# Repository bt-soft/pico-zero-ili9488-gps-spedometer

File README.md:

# Pico GPS Sebességmérő Motorokhoz

Ez a projekt egy fejlett Raspberry Pi Pico alapú GPS sebességmérő, amely egy ILI9488 TFT kijelzőt használ a sebesség, idő, magasság és a közeli sebességmérő kamerák (trafipaxok) megjelenítésére. A készülék kifejezetten motorkerékpár-vezetők számára lett tervezve, hogy segítse őket a biztonságos és szabályos közlekedésben.

<div style="display: flex; gap: 8px;">

</div>

## Főbb Jellemzők

### 🚀 **Sebességmérés és Navigáció**
- **Valós idejű sebességmérés** GPS adatok alapján 
- **Nagy méretű sebességmérő** vizuális megjelenítés
- **Műholdak száma** és jelerősség megjelenítése
- **Tengerszint feletti magasság** mérése és megjelenítése

### 🕐 **Időkezelés és Pozicionálás**
- **Pontos idő** megjelenítése GPS szinkronizációval
- **Automatikus időzóna** beállítás
- **Téli/nyári időszámítás** támogatása

### 🚨 **Trafipax Figyelmeztető Rendszer**
- **Intelligens sebességmérő kamera (trafipax) adatbázis** kezelése
- **Közeledési figyelmeztetés** max 1500 méteres beállítható távolságon belül (kör alapú megközelítés)
- **Vizuális riasztás**: piros háttér közeledéskor, narancssárga távolodáskor
- **Hangos figyelmeztetés** szirénával közeledés esetén
- **Távolság megjelenítése** a legközelebbi trafipaxig
- **Stabil állapotváltás** GPS pontatlansággal szembeni védelemmel

### 🎨 **Megjelenítés és Felhasználói Felület**
- **3.5" ILI9488 480x320 színes TFT kijelző**
- **Nagyméretű, jól olvasható** betűtípusok
- **Automatikusan állított háttérvilágítás** a környezeti fényerőkhöz igazodva

### 💾 **Adatkezelés és Testre Szabás**
- **LittleFS fájlrendszer** a beépített flash memóriában
- **CSV formátumú trafipax adatbázis** egyszerű frissítéshez
- **Konfigurálható figyelmeztetési távolságok**
- **Személyre szabható megjelenítési beállítások**

## Hardver Követelmények

- **Mikrokontroller:** Raspberry Pi Pico vagy Pico Zero (RP2040 alapú)
- **Kijelző:** ILI9488 3.5" 480x320 SPI TFT kijelző érintőképernyővel
- **GPS Modul:** Bármilyen UART-alapú GPS modul (pl. NEO-6M, NEO-8M), NMEA mondatok parszolása
- **Tápellátás:** 5V USB vagy külső tápegység
- **Rajz és NYÁK:** A kapcsolási rajzok, panel tervek a `kicad/` mappában

## Szoftver Architektúra

- **Fejlesztői környezet:** [PlatformIO](https://platformio.org/) a [Visual Studio Code](https://code.visualstudio.com/)-ban
- **Framework:** Arduino Framework [Raspberry Pi Pico](https://github.com/maxgerhardt/platform-raspberrypi) támogatással
- **Többmagos feldolgozás:** Dual-core RP2040 kihasználása
  - **Core 0:** Fő alkalmazás logika, kijelzőkezelés
  - **Core 1:** GPS adatfeldolgozás, háttér számítások

### Főbb Könyvtárak
- `bodmer/TFT_eSPI` - Kijelzőkezelés és sprite renderelés
- `mikalhart/TinyGPSPlus` - GPS adatfeldolgozás és koordináta számítások  
- `LittleFS` - Beépített fájlrendszer kezelés
- `NonBlockingDallas` - Hőmérséklet szenzor
- `FastLED` - Zeró intergrált RGB LED vezérlés (státusz jelzéshez, debug funkció)

## Telepítés és Üzembe Helyezés

### 1. Fejlesztői Környezet Beállítása
```bash
# Git repository klónozása
git clone https://github.com/bt-soft/pico-zero-ili9488-gps-spedometer.git
cd pico-zero-ili9488-gps-spedometer

# Visual Studio Code megnyitása
code .
```

### 2. Trafipax Adatbázis Feltöltése
A készülék kezdeti használatához fel kell tölteni a trafipax adatbázist:

```bash
# Adatbázis feltöltése LittleFS-be
pio run --target uploadfs
```

## Trafipax Adatbázis Kezelése

### Adatbázis Formátum
A `data/trafipaxes.csv` fájl formátuma:
```csv
Vármegye,Település neve,Útszám,Kilométer-szelvény/utca,GPS koordináta szélesség,GPS koordináta hosszúság
Pest,Alsónémedi,,Haraszti út 6.,47.315308,19.163705
Pest,Biatorbágy,,M1 17+000,47.468751,18.864466
Pest,Budapest,,M0,47.589436,19.142904
Pest,Budapest,,M0 14+450,47.400208,19.011840
...
```

### Adatbázis Frissítése

#### Feltöltés 
```bash
# 1. Új trafipaxes.csv elhelyezése a data/ mappában
# 2. Fájlrendszer feltöltése
pio run --target uploadfs

# 3. Készülék újraindítása (automatikus)
```

### Adatforrások
- **Magyarország:** [AutópályaMatrica.hu](https://www.autopalyamatrica.hu/fix-traffipax-lista-veda-terkep) adatai

**⚠️ Figyelmeztetés:** A trafipax adatok tájékoztató jellegűek. 

## Konfiguráció és Testreszabás
 A főbb hardveres pin hozzárendelések a `include/pins.h` fájlban találhatók, ezek igény szerint módosíthatók a saját bekötéshez.

 ### Főbb Pin Definíciók

 - **Serial1 TX/RX (GPS modul):**
   - TX: GPIO 12 (`PIN_SERIAL1_TX_NEW`)
   - RX: GPIO 13 (`PIN_SERIAL1_RX_NEW`)
   - Használat: A GPS modul csatlakoztatásához a soros portot át kell állítani ezekre a pinekre a `Serial1.setRX(PIN_SERIAL1_RX_NEW)` és `Serial1.setTX(PIN_SERIAL1_TX_NEW)` hívásokkal a `Serial1.begin()` előtt.

 - **TFT háttérvilágítás vezérlés:**
   - GPIO 1 (`PIN_TFT_BACKGROUND_LED`)
   - Automatikus fényerő szabályzás a környezeti fény alapján.

 - **Fényérzékelő:**
   - A1 (`PIN_LIGHT_SENSOR`)
   - A háttérvilágítás automatikus szabályzásához.

 - **Hőmérséklet szenzor (DS18B20):**
   - GPIO 8 (`PIN_DS18B20_TEMP_SENSOR`)

 - **Tápfeszültség mérés:**
   - VBUS: A0 (`PIN_VBUS_EXTERNAL_MEASURE_INPUT`)
   - VSYS: A2 (`PIN_VSYS_EXTERNAL_MEASURE_INPUT`)

 - **Buzzer (hangjelzés):**
   - GPIO 9 (`PIN_BUZZER`)

 A fenti pinek módosíthatók a saját hardverhez igazítva a `include/pins.h` fájlban. További testreszabási lehetőségek:
 - Trafipax figyelmeztetési távolság, hangjelzés, kijelző fényerő, stb. konfigurálható a szoftverben.

## Fejlesztői Információk

### Projekt Struktúra

```
├── src/                       # Fő forráskód és implementációk
│   ├── main.cpp               # Főprogram
│   ├── Config.cpp/.h          # Konfigurációs logika
│   ├── GpsManager.cpp/.h      # GPS kezelés
│   ├── DebugDataInspector.cpp/.h
│   ├── MessageDialog.cpp/.h
│   ├── SatelliteDb.cpp/.h
│   ├── Screen*                # Különböző képernyő logikák
│   ├── SensorUtils.cpp/.h     # Szenzor segédfüggvények
│   ├── TftBackLightAdjuster.cpp/.h
│   ├── TraffipaxManager.cpp/.h
│   ├── UIDialogBase.cpp/.h
│   ├── UIScreen.cpp/.h
│   ├── Utils.cpp/.h
│   └── ValueChangeDialog.cpp/.h
│   └── ... további modulok
├── include/                   # Header fájlok
│   ├── pins.h                 # Pin definíciók
│   ├── ... további .h fájlok
├── data/                      # LittleFS fájlok
│   └── trafipaxes.csv         # Trafipax adatbázis
├── Docs/                      # Dokumentáció
│   ├── pictures/              # Képek, renderelt ábrák
│   ├── TFT_eSPI/              # Kijelző setup és példák
│   └── trafipaxes.csv         # Minta adatbázis
├── kicad/                     # Hardver tervek
│   ├── pico-gps-spedometer/   # Fő kapcsolási rajzok, PCB
│   ├── pico-gps-spedometer-accu/ # Akkumulátoros verzió
├── platformio.ini             # PlatformIO konfiguráció
├── upload_fs.py               # Fájlrendszer feltöltő script
├── info.txt                   # Projekt információk
└── .vscode/                   # VS Code beállítások
```

**Fontos:** A TFT_eSPI könyvtár megfelelő működéséhez a `Docs/TFT_eSPI/User_Setup.h` fájlt be kell másolni a következő helyre:

```
.pio\libdeps\pico\TFT_eSPI\User_Setup.h
```

Ez biztosítja, hogy a kijelző beállítások megfelelően érvényesüljenek a build során. Ha módosítod a kijelző vagy a pinek konfigurációját, ezt a fájlt frissíteni kell és újra bemásolni a fenti könyvtárba.

---
**Fejlesztő:** BT-Soft  
**Blog:** [https://electrodiy.blog.hu/](https://electrodiy.blog.hu/)  
**GitHub:** [https://github.com/bt-soft](https://github.com/bt-soft)  

---

**⚠️ Biztonsági figyelmeztetés:** Ez az eszköz csak tájékoztató célokat szolgál. A közlekedési szabályok betartása a vezető felelőssége. A készülék használata nem mentesít a figyelmes és szabályos vezetés kötelezettsége alól.

## Képek a POC projektről

<div style="display: flex; gap: 8px;">

</div>

<div style="display: flex; gap: 8px;">

</div>

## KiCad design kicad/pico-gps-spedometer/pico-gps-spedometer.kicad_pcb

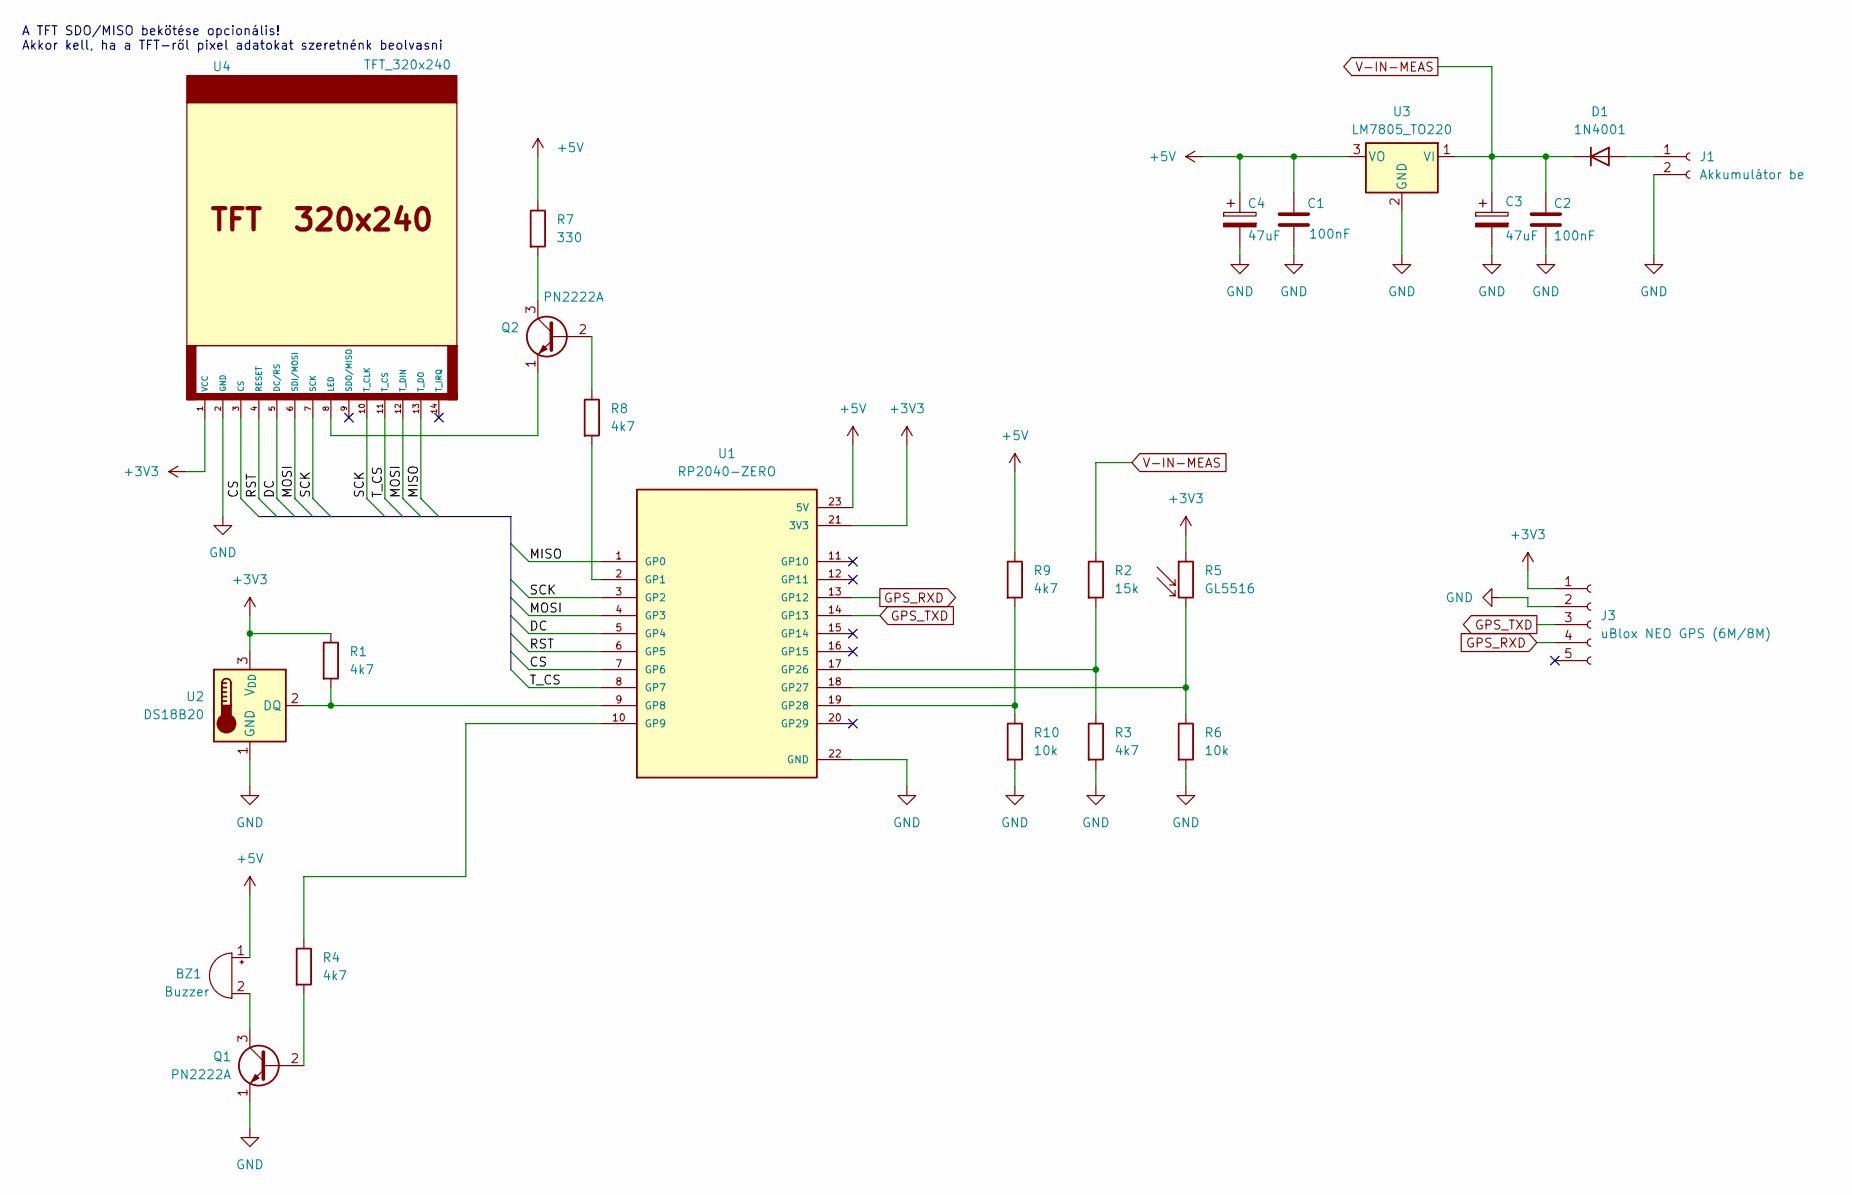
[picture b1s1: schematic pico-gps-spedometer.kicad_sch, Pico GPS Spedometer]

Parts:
BZ1: Buzzer; Buzzer_12x9.5RM7.6
C1, C2: 100nF; C_Disc_D5.0mm_W2.5mm_P2.50mm
C3, C4: 47uF; CP_Radial_D7.5mm_P2.50mm
D1: 1N4001; D_DO-41_SOD81_P10.16mm_Horizontal
J1: Akkumulátor be; PinHeader_1x02_P2.54mm_Vertical
J3: uBlox NEO GPS (6M/8M); PinSocket_1x05_P2.54mm_Vertical
Q1, Q2: PN2222A; TO-92_Inline
R1, R3, R4, R8, R9: 4k7; R_Axial_DIN0204_L3.6mm_D1.6mm_P7.62mm_Horizontal
R2: 15k; R_Axial_DIN0204_L3.6mm_D1.6mm_P7.62mm_Horizontal
R5: GL5516; PinHeader_1x02_P2.54mm_Vertical
R6, R10: 10k; R_Axial_DIN0204_L3.6mm_D1.6mm_P7.62mm_Horizontal
R7: 330; R_Axial_DIN0204_L3.6mm_D1.6mm_P7.62mm_Horizontal
U1: RP2040-ZERO; MODULE_RP2040-ZERO; PARTREV NA
U2: DS18B20; PinHeader_1x03_P2.54mm_Vertical
U3: LM7805_TO220; TO-220-3_Horizontal_TabDown
U4: TFT_320x240; PinSocket_1x14_P2.54mm_Vertical

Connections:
+3V3: J3.1, R1.1, R5.1, U1.21 (3V3), U2.3 (V_{DD}), U4.1 (VCC)
+5V: BZ1.1 (+), C1.1, C4.1, R7.1, R9.1, U1.23 (5V), U3.3 (VO)
/CS: U1.7 (GP6), U4.3 (CS)
/DC: U1.5 (GP4), U4.5 (DC/RS)
/MISO: U1.1 (GP0), U4.13 (T_DO)
/MOSI: U1.4 (GP3), U4.6 (SDI/MOSI), U4.12 (T_DIN)
/RST: U1.6 (GP5), U4.4 (RESET)
/SCK: U1.3 (GP2), U4.7 (SCK), U4.10 (T_CLK)
/T_CS: U1.8 (GP7), U4.11 (T_CS)
GND: C1.2, C2.2, C3.2, C4.2, J1.2, J3.2, Q1.1 (E), R3.2, R6.2, R10.2, U1.22 (GND), U2.1 (GND), U3.2 (GND), U4.2 (GND)
GPS_RXD: J3.4, U1.13 (GP12)
GPS_TXD: J3.3, U1.14 (GP13)
unnamed: BZ1.2 (-), Q1.3 (C)
unnamed: D1.2 (A), J1.1
unnamed: Q1.2 (B), R4.2
unnamed: Q2.2 (B), R8.1
unnamed: Q2.3 (C), R7.2
unnamed: Q2.1 (E), U4.8 (LED)
unnamed: R8.2, U1.2 (GP1)
unnamed: R1.2, U1.9 (GP8), U2.2 (DQ)
unnamed: R4.1, U1.10 (GP9)
unnamed: R2.2, R3.1, U1.17 (GP26)
unnamed: R5.2, R6.1, U1.18 (GP27)
unnamed: R9.2, R10.1, U1.19 (GP28)
V-IN-MEAS: C2.1, C3.1, D1.1 (K), R2.1, U3.1 (VI)

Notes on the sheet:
A TFT SDO/MISO bekötése opcionális! Akkor kell, ha a TFT-ről pixel adatokat szeretnénk beolvasni

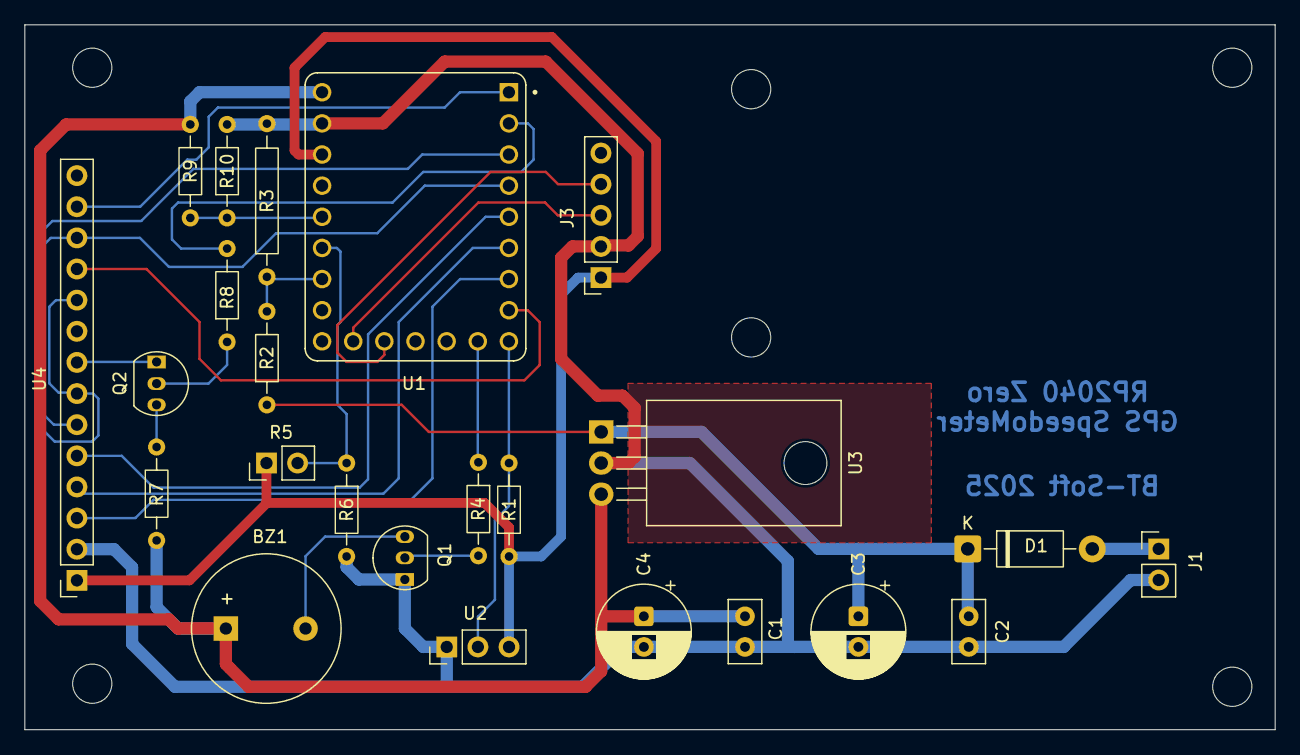
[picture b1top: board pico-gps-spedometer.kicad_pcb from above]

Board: 2 copper layers, 102.0 x 57.5 mm, 24 parts (0 on the bottom side), 25 nets.

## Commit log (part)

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2025-01-04 Működő verzió
2025-08-09 Add support for TFT display and GPS functionality with daylight saving adjustments
    - Created a stripped down User_Setup.h for ILI9488 display configuration.
    - Implemented DaylightSaving class to handle time zone and summer time corrections.
    - Added commons.h for color schemes and font sizes.
    - Developed linearMeter.h for vertical and horizontal linear meters.
    - Created ringMeter.h for displaying values in a circular format with rainbow colors.
    - Configured platformio.ini for project dependencies and build settings.
2025-08-09 Enhance documentation and comments in linearMeter and ringMeter; update speed value handling in main.cpp
2025-08-09 Enhance verticalLinearMeter and ringMeter functions for improved text rendering and color handling
2025-08-09 Remove unnecessary debug serial prints and improve temperature change handling comments
2025-08-10 Fix speed value handling in displayValues function for accurate ringMeter display
2025-08-10 Refactor verticalLinearMeter to use TFT_eSprite for improved rendering and memory management
2025-08-10 Remove random speed value generation for accurate display in displayValues function
2025-08-10 Remove lock file for pico-gps-spedometer PCB
2025-08-10 Add ASCII conversion utility and demo simulation for Trafipax alerts
2025-08-12 egyoldalas nyák
2025-08-14 Update alert bar height and adjust text positioning in Trafipax alert display
2025-08-14 Implement Trafipax demo functionality with simulation of approach and departure phases
2025-08-16 Update README to enhance project description, features, hardware requirements, software architecture, and installation instructions
2025-08-16 Remove obsolete files from the project
    - Deleted map.dat and version.dat from the Docs/tiveda directory as they are no longer needed.
    - Removed an outdated backup zip file of the pico GPS speedometer from the kicad backups directory.
2025-08-16 Add splash screen and display version information on startup
2025-08-16 Enable demo mode for speed and satellite values in displayValues function
2025-08-17 Remove commented-out modern splash screen code for cleaner implementation
2025-08-17 Add TrafipaxManager class and related functionality
    - Introduced TrafipaxManager class to handle traffic camera data management.
    - Removed TafipaxList class and its associated files.
    - Implemented methods for loading traffic camera data from CSV, checking proximity, and demo functionalities.
    - Updated ConfigData structure to include gpsTrafiAlarmEnabled flag.
    - Adjusted main application logic to utilize TrafipaxManager for traffic camera operations.
2025-08-17 Refactor Trafipax configuration and alert handling: - Update Config_t structure to reorder gpsTrafiAlarmDistance and gpsTrafiAlarmEnabled. - Change MAX_TAFIPAX to MAX_TRAFIPAX_COUNT for consistency. 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
2025-08-17 Add demo mode functionality to TrafipaxManager and main logic
2025-08-17 Enhance Settings and Button classes with new functionalities for brightness control and UI improvements
2025-08-17 Refactor Settings class for improved button layout and add screen title rendering functionality
2025-08-17 Enhance Button and Settings classes with visual feedback, layout optimizations, and modern design elements
2025-08-17 Refactor code structure and remove redundant functions for improved readability and maintainability
2025-08-17 Refactor GPS GSV message handling and streamline satellite data processing
2025-08-17 Refactor GPS GSV message handling to improve satellite data processing and tracking accuracy
2025-08-23 Refactor GPS handling and add satellite database management; rename adjust method to loop in TftBackLightAdjuster, implement GpsManager and SatelliteDb classes for improved satellite data processing 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
2025-08-23 Update LED color indication and improve satellite database handling in GpsManager
2025-08-23 Initialize FastLED for LED control in GpsManager and fix typo in LED blinking comment
2025-08-23 Add debugging options for GPS data and RGB LED control; remove unused ConfigData.h
2025-08-23 Fix icon positioning in drawContent method; adjust GPS accuracy and speedometer icon placements for improved layout.
2025-08-23 Add max speed tracking and display in handleOwnLoop; enhance speedometer feedback with dynamic updates
2025-08-23 Add sensor utility integration for battery and temperature readings in handleOwnLoop; update vertical linear meters to reflect real-time values.
2025-08-23 Refactor DebugDataInspector header file for improved clarity and maintainability
2025-08-23 Update sensor initialization and maintenance in main setup and loop; add new main.cpp_dallas file for reference
2025-08-23 Refactor SensorUtils to implement NonBlockingDallas for temperature handling; update initialization and loop methods
2025-08-23 Refactor SensorUtils to use static objects for Dallas temperature sensor; re-enable sensor maintenance in main loop
2025-08-24 Adjust text positioning for units and date/time display; improve layout consistency
2025-08-24 Add temperature mode state and sprite update timer; adjust sensor cache timeout
2025-08-24 Rename temperatureMode to externalTemperatureMode for clarity; update related logic and text positioning
2025-08-24 Add Info and Setup screens with navigation buttons; refactor layout components
2025-08-24 Implement ScreenSats class for detailed GPS satellite display; refactor screen management and update related components
2025-08-24 Refactor ScreenSats class: remove unused direct drawing methods and implement getColorBySnr function for cleaner code
2025-08-24 Enhance satellite data management: add sorting options and update UI interactions for better user experience
2025-08-24 Refactor screen setup classes: streamline back button functionality and improve layout component organization
2025-08-24 Refactor configuration and screen setup: improve GPS settings organization and update button labels for clarity
2025-08-24 Refactor ScreenTFTSetup: add manual brightness button and enhance auto brightness functionality
2025-08-24 Refactor ValueChangeDialog: enhance safe arithmetic checks and ensure button redraw on state change
2025-08-29 Refactor ScreenGPSSetup and related components: enhance layout and button functionality, add GPS traffic alarm distance adjustment
2025-08-29 Enhance GPS display: adjust satellite count position and add current GPS mode display
2025-08-29 Add DisplayData structure and data collection methods for real and demo modes
2025-08-29 Update demo mode GPS accuracy: adjust HDOP range to improve data realism
2025-08-29 Update splash screen: change font style and size for traffic count display
2025-08-29 Update date and time display formatting: adjust text padding and reposition time string for improved layout
2025-08-30 Refactor header guards to use #pragma once for consistency across multiple files
    - Updated all header files to replace traditional include guards with #pragma once for improved readability and maintainability.
    - Modified GpsManager to enhance LocalDateTime structure with separate validity flags for time and date.
    - Adjusted button dimensions in ValueChangeDialog for better UI consistency.
    - Updated button gap constant in MessageDialog to use the newly defined BUTTONS_GAP.
    - Improved comments and documentation for clarity in various functions across multiple files.
2025-08-30 Update text padding in handleOwnLoop for improved layout
2025-08-30 Refactor TraffipaxManager: Update demo handling logic and replace static demo coordinates with dynamic values
2025-08-30 Refactor TraffipaxManager: Improve debug output for demo traffic selection
2025-08-30 Remove debug wait for serial definition from defines.h
2025-08-30 Refactor TraffipaxManager: Enhance debug output formatting in demo phase processing
2025-08-30 Refactor ScreenMain and ScreenDebugSetup: Rename batteryVoltage to busVoltage for clarity and update layout logic for button positioning
2025-08-30 Refactor GpsManager: Update LED pin definitions and initialization for clarity and consistency
2025-08-30 Refactor Config: Update comment for clarity regarding internal LED behavior
2025-08-31 Refactor ScreenMain and UIScreen: Optimize state variables, extract demo logic, and implement UI value update helper function
2025-08-31 Refactor ScreenInfo: Improve formatting and readability of UIButton creation in layoutComponents
2025-08-31 Refactor ScreenSats: Reorder includes and remove redundant comment on table width
2025-08-31 Refactor Siren Handling: Update siren parameters for improved alert functionality and ensure non-blocking siren handling in the main loop
2025-08-31 Refactor ScreenSats and ScreenMain: Improve button layout and text positioning for better UI clarity
2025-08-31 Refactor ScreenMain: Adjust calendar and time string positioning for improved UI alignment
2025-08-31 Refactor ScreenInfo: Enhance drawContent method to add second column for heap memory statistics
2025-08-31 Refactor ScreenSats: Improve satellite table display and add beeper functionality on header touch events
2025-08-31 Refactor ScreenInfo: Update text color and position for GPS Speedometer display
2025-08-31 Refactor ScreenMain: Implement dark button color scheme for Info and Setup buttons
2025-09-01 Refactor: Optimize string handling with buffers across multiple screens and utilities
2025-09-04 Refactor TftBackLightAdjuster: Add debug log for backlight brightness adjustment
2025-09-05 Refactor CPU frequency settings: Update F_CPU to 133MHz and remove legacy configuration
2025-09-06 Refactor drawContent and handleOwnLoop: Improve formatting and add external voltage reading
2025-09-06 Refactor handleOwnLoop: Add conditional GPS boot time display logic
2025-09-06 Refactor screensaver logic and backlight control: Enhance screensaver activation conditions and adjust backlight management during screensaver state
2025-09-06 Remove debug logging for backlight control in loop1
2025-09-06 Refactor ScreenScreenSaver: Update variable types for position calculations and adjust font size for improved layout
2025-09-06 Refactor configuration handling: Move external temperature and voltage modes to ConfigData structure, update references in ScreenMain and ScreenScreenSaver
2025-09-10 Update visible layers and fix footprint mismatch in pico-gps-spedometer project
    - Changed the visible layers setting in the .kicad_prl file to include a new layer.
    - Updated the footprint mismatch entry in the .kicad_pro file to correct the dimensions for a specific component.
2025-09-10 readme.md
2025-09-12 Add lock file for pico-gps-spedometer schematic to prevent concurrent edits
2025-09-12 Update README.md to include detailed hardware pin assignments and configuration options for GPS and TFT display
2025-09-12 Update README.md to include instructions for TFT_eSPI library setup and configuration
2025-09-12 Fix formatting in README.md by adding a separator before developer information
2025-09-12 Update image display in README.md for better visibility
2025-09-12 Reorder images in README.md for improved layout consistency
2025-09-12 Reorganize image layout in README.md for improved display and consistency
2025-09-12 Fix duplicate image entries in README.md for improved layout consistency
2025-09-14 Remove outdated backup zip files for pico-gps-spedometer
2025-09-14 Refactor sensor initialization and maintenance to setup1 and loop1 for improved structure
2025-09-15 Enhance configuration management with change callbacks and update related components
2025-09-15 Refactor GpsManager to use configuration change callbacks for improved state management
2025-09-15 Initialize backlight level in TftBackLightAdjuster::begin for immediate brightness setting
